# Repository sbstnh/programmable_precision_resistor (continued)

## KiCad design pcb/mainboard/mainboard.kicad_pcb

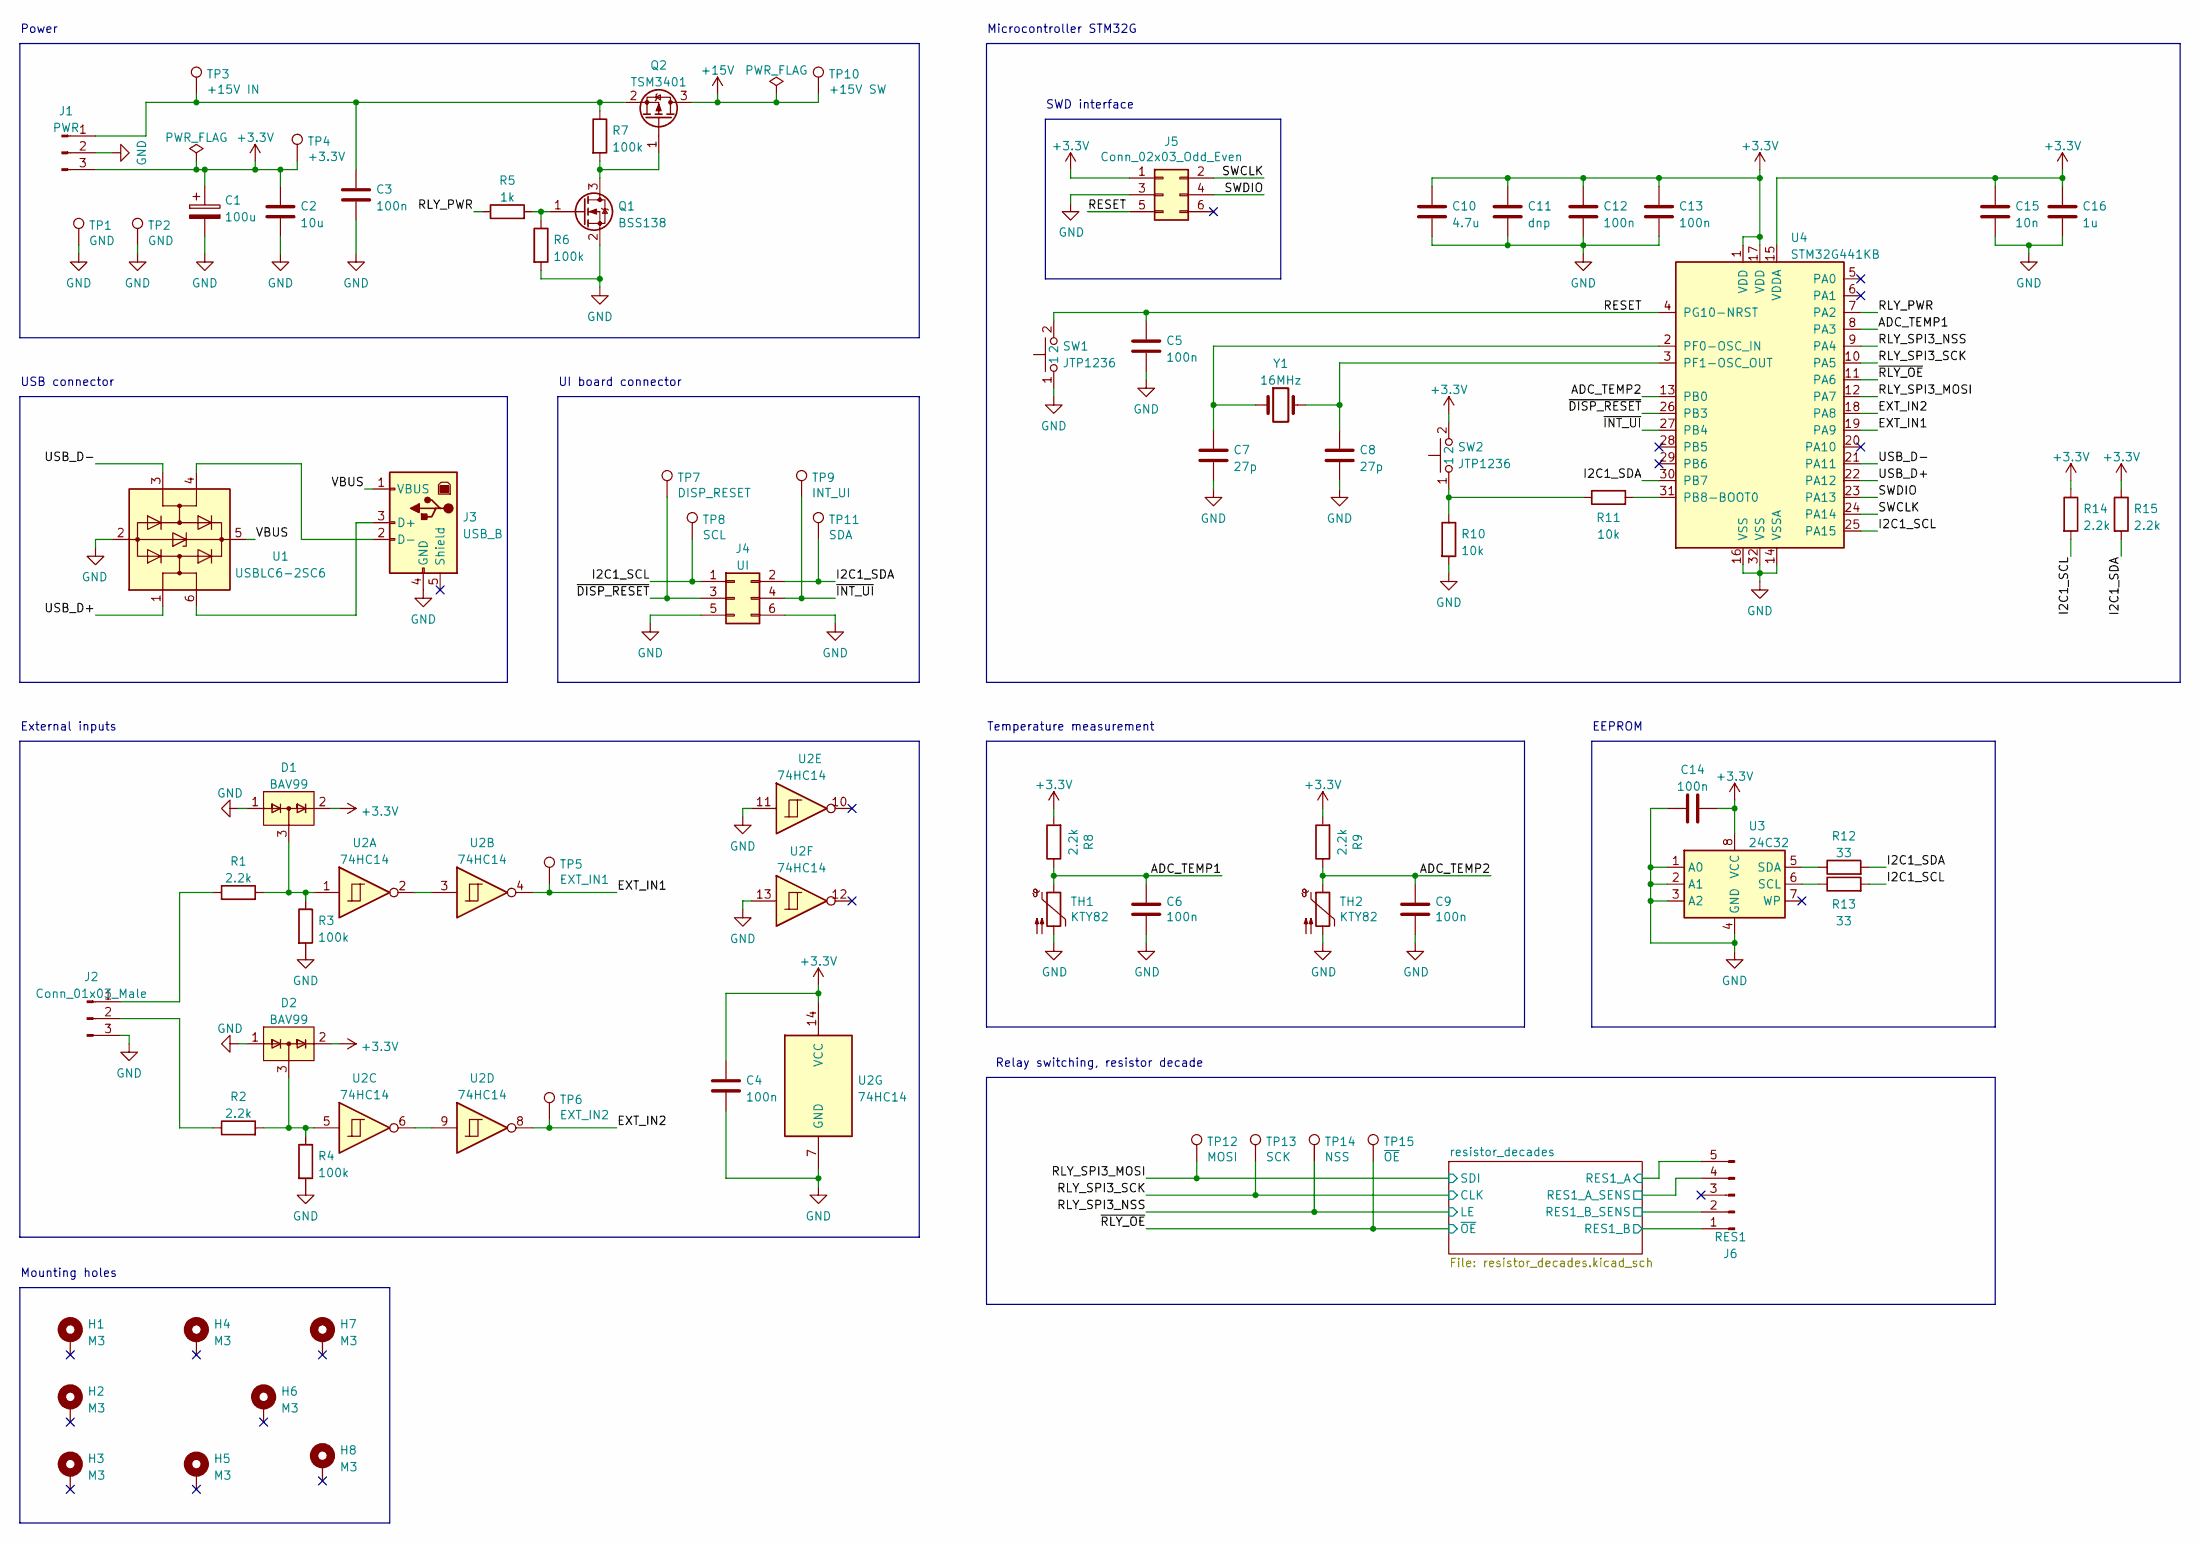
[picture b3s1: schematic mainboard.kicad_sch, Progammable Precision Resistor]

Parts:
C1: 100u; CP_EIA-7343-31_Kemet-D_Pad2.25x2.55mm_HandSolder
C2: 10u; C_0805_2012Metric_Box
C3, C4, C5, C6, C9, C12, C13, C14: 100n; C_0805_2012Metric_Box
C7, C8: 27p; C_0805_2012Metric_Box
C10: 4.7u; C_0805_2012Metric_Box
C11: dnp; C_0805_2012Metric_Box
C15: 10n; C_0805_2012Metric_Box
C16: 1u; C_0805_2012Metric_Box
D1, D2: BAV99; SOT-23
H1, H2, H3, H4, H5, H6, H7, H8: M3; MountingHole_3.2mm_M3_DIN965_Pad
J1: PWR; Molex_KK-254_AE-6410-03A_1x03_P2.54mm_Vertical
J2: Conn_01x03_Male; PhoenixContact_MSTBA_2,5_3-G_1x03_P5.00mm_Horizontal
J3: USB_B; USB_B_Lumberg_2411_02_Horizontal
J4: UI; IDC-Header_2x03_P2.54mm_Vertical
J5: Conn_02x03_Odd_Even; IDC-Header_2x03_P2.54mm_Vertical
J6: RES1; Molex_KK-396_A-41791-0005_1x05_P3.96mm_Vertical
Q1: BSS138; SOT-23
Q2: TSM3401; SOT-23
R1, R2, R8, R9, R14, R15: 2.2k; R_0805_2012Metric_Box
R3, R4, R6, R7: 100k; R_0805_2012Metric_Box
R5: 1k; R_0805_2012Metric_Box
R10, R11: 10k; R_0805_2012Metric_Box
R12, R13: 33; R_0805_2012Metric_Box
SW1, SW2: JTP1236
TH1, TH2: KTY82; SOT-23
TP1, TP2: GND; TestPoint_Loop_D1.80mm_Drill1.0mm_Beaded
TP3: +15V IN; TestPoint_Loop_D1.80mm_Drill1.0mm_Beaded
TP4: +3.3V; TestPoint_Loop_D1.80mm_Drill1.0mm_Beaded
TP5: EXT_IN1; TestPoint_Loop_D1.80mm_Drill1.0mm_Beaded
TP6: EXT_IN2; TestPoint_Loop_D1.80mm_Drill1.0mm_Beaded
TP7: DISP_RESET; TestPoint_Loop_D1.80mm_Drill1.0mm_Beaded
TP8: SCL; TestPoint_Loop_D1.80mm_Drill1.0mm_Beaded
TP9: INT_UI; TestPoint_Loop_D1.80mm_Drill1.0mm_Beaded
TP10: +15V SW; TestPoint_Loop_D1.80mm_Drill1.0mm_Beaded
TP11: SDA; TestPoint_Loop_D1.80mm_Drill1.0mm_Beaded
TP12: MOSI; TestPoint_Loop_D1.80mm_Drill1.0mm_Beaded
TP13: SCK; TestPoint_Loop_D1.80mm_Drill1.0mm_Beaded
TP14: NSS; TestPoint_Loop_D1.80mm_Drill1.0mm_Beaded
TP15: ~{OE}; TestPoint_Loop_D1.80mm_Drill1.0mm_Beaded
U1: USBLC6-2SC6; SOT-23-6
U2: 74HC14; SOIC-14_3.9x8.7mm_P1.27mm
U3: 24C32; SO-8_3.9x4.9mm_P1.27mm
U4: STM32G441KB; LQFP-32_7x7mm_P0.8mm
Y1: 16MHz; Crystal_HC49-4H_Vertical

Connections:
+3.3V: C1.1, C2.1, C4.1, C10.1, C11.1, C12.1, C13.1, C14.2, C15.1, C16.1, D1.2 (A), D2.2 (A), J1.3, J5.1, R8.2, R9.2, R14.1, R15.1, SW2.2, TP4.1, U2.14 (VCC), U3.8 (VCC), U4.1 (VDD), U4.15 (VDDA), U4.17 (VDD); also elsewhere on the board
+15V: Q2.3 (D), TP10.1; also elsewhere on the board
/ADC_TEMP1: C6.1, R8.1, TH1.1, U4.8 (PA3)
/ADC_TEMP2: C9.1, R9.1, TH2.1, U4.13 (PB0)
/EXT_IN1: TP5.1, U2.4, U4.19 (PA9)
/EXT_IN2: TP6.1, U2.8, U4.18 (PA8)
/I2C1_SCL: J4.1, R13.2, R14.2, TP8.1, U4.25 (PA15)
/I2C1_SDA: J4.2, R12.2, R15.2, TP11.1, U4.30 (PB7)
/RESET: C5.1, J5.5, SW1.2, U4.4 (PG10-NRST)
/RLY_PWR: R5.1, U4.7 (PA2)
/RLY_SPI3_MOSI: TP12.1, U4.12 (PA7); also elsewhere on the board
/RLY_SPI3_NSS: TP14.1, U4.9 (PA4); also elsewhere on the board
/RLY_SPI3_SCK: TP13.1, U4.10 (PA5); also elsewhere on the board
/SWCLK: J5.2, U4.24 (PA14)
/SWDIO: J5.4, U4.23 (PA13)
/USB_D+: U1.1 (I/O1), U4.22 (PA12)
/USB_D-: U1.3 (I/O2), U4.21 (PA11)
/VBUS: J3.1 (VBUS), U1.5 (VBUS)
/resistor_decades/RES1_A: J6.4, J6.5; also elsewhere on the board
/resistor_decades/RES1_B: J6.1, J6.2; also elsewhere on the board
/~DISP_RESET: J4.3, TP7.1, U4.26 (PB3)
/~INT_UI: J4.4, TP9.1, U4.27 (PB4)
/~RLY_OE: TP15.1, U4.11 (PA6); also elsewhere on the board
GND: C1.2, C2.2, C3.2, C4.2, C5.2, C6.2, C7.2, C8.2, C9.2, C10.2, C11.2, C12.2, C13.2, C14.1, C15.2, C16.2, D1.1 (K), D2.1 (K), J1.2, J2.3, J3.4 (GND), J4.5, J4.6, J5.3, Q1.2 (S), R3.2, R4.2, R6.2, R10.2, SW1.1, TH1.2, TH2.2, TP1.1, TP2.1, U1.2 (GND), U2.7 (GND), U2.11, U2.13, U3.1 (A0), U3.2 (A1), U3.3 (A2), U3.4 (GND), U4.14 (VSSA), U4.16 (VSS), U4.32 (VSS); also elsewhere on the board
unnamed: D1.3 (K), R1.2, R3.1, U2.1
unnamed: D2.3 (K), R2.2, R4.1, U2.5
unnamed: C3.1, J1.1, Q2.2 (S), R7.1, TP3.1
unnamed: J2.1, R1.1
unnamed: J2.2, R2.1
unnamed: J3.3 (D+), U1.6 (I/O1)
unnamed: J3.2 (D-), U1.4 (I/O2)
unnamed: Q1.3 (D), Q2.1 (G), R7.2
unnamed: Q1.1 (G), R5.2, R6.1
unnamed: R10.1, R11.1, SW2.1
unnamed: U2.2, U2.3
unnamed: U2.6, U2.9
unnamed: R13.1, U3.6 (SCL)
unnamed: R12.1, U3.5 (SDA)
unnamed: R11.2, U4.31 (PB8-BOOT0)
unnamed: C7.1, U4.2 (PF0-OSC_IN), Y1.1
unnamed: C8.1, U4.3 (PF1-OSC_OUT), Y1.2

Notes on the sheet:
EEPROM
Power
Microcontroller STM32G
Mounting holes
USB connector
External inputs
Temperature measurement
Relay switching, resistor decade
SWD interface
UI board connector

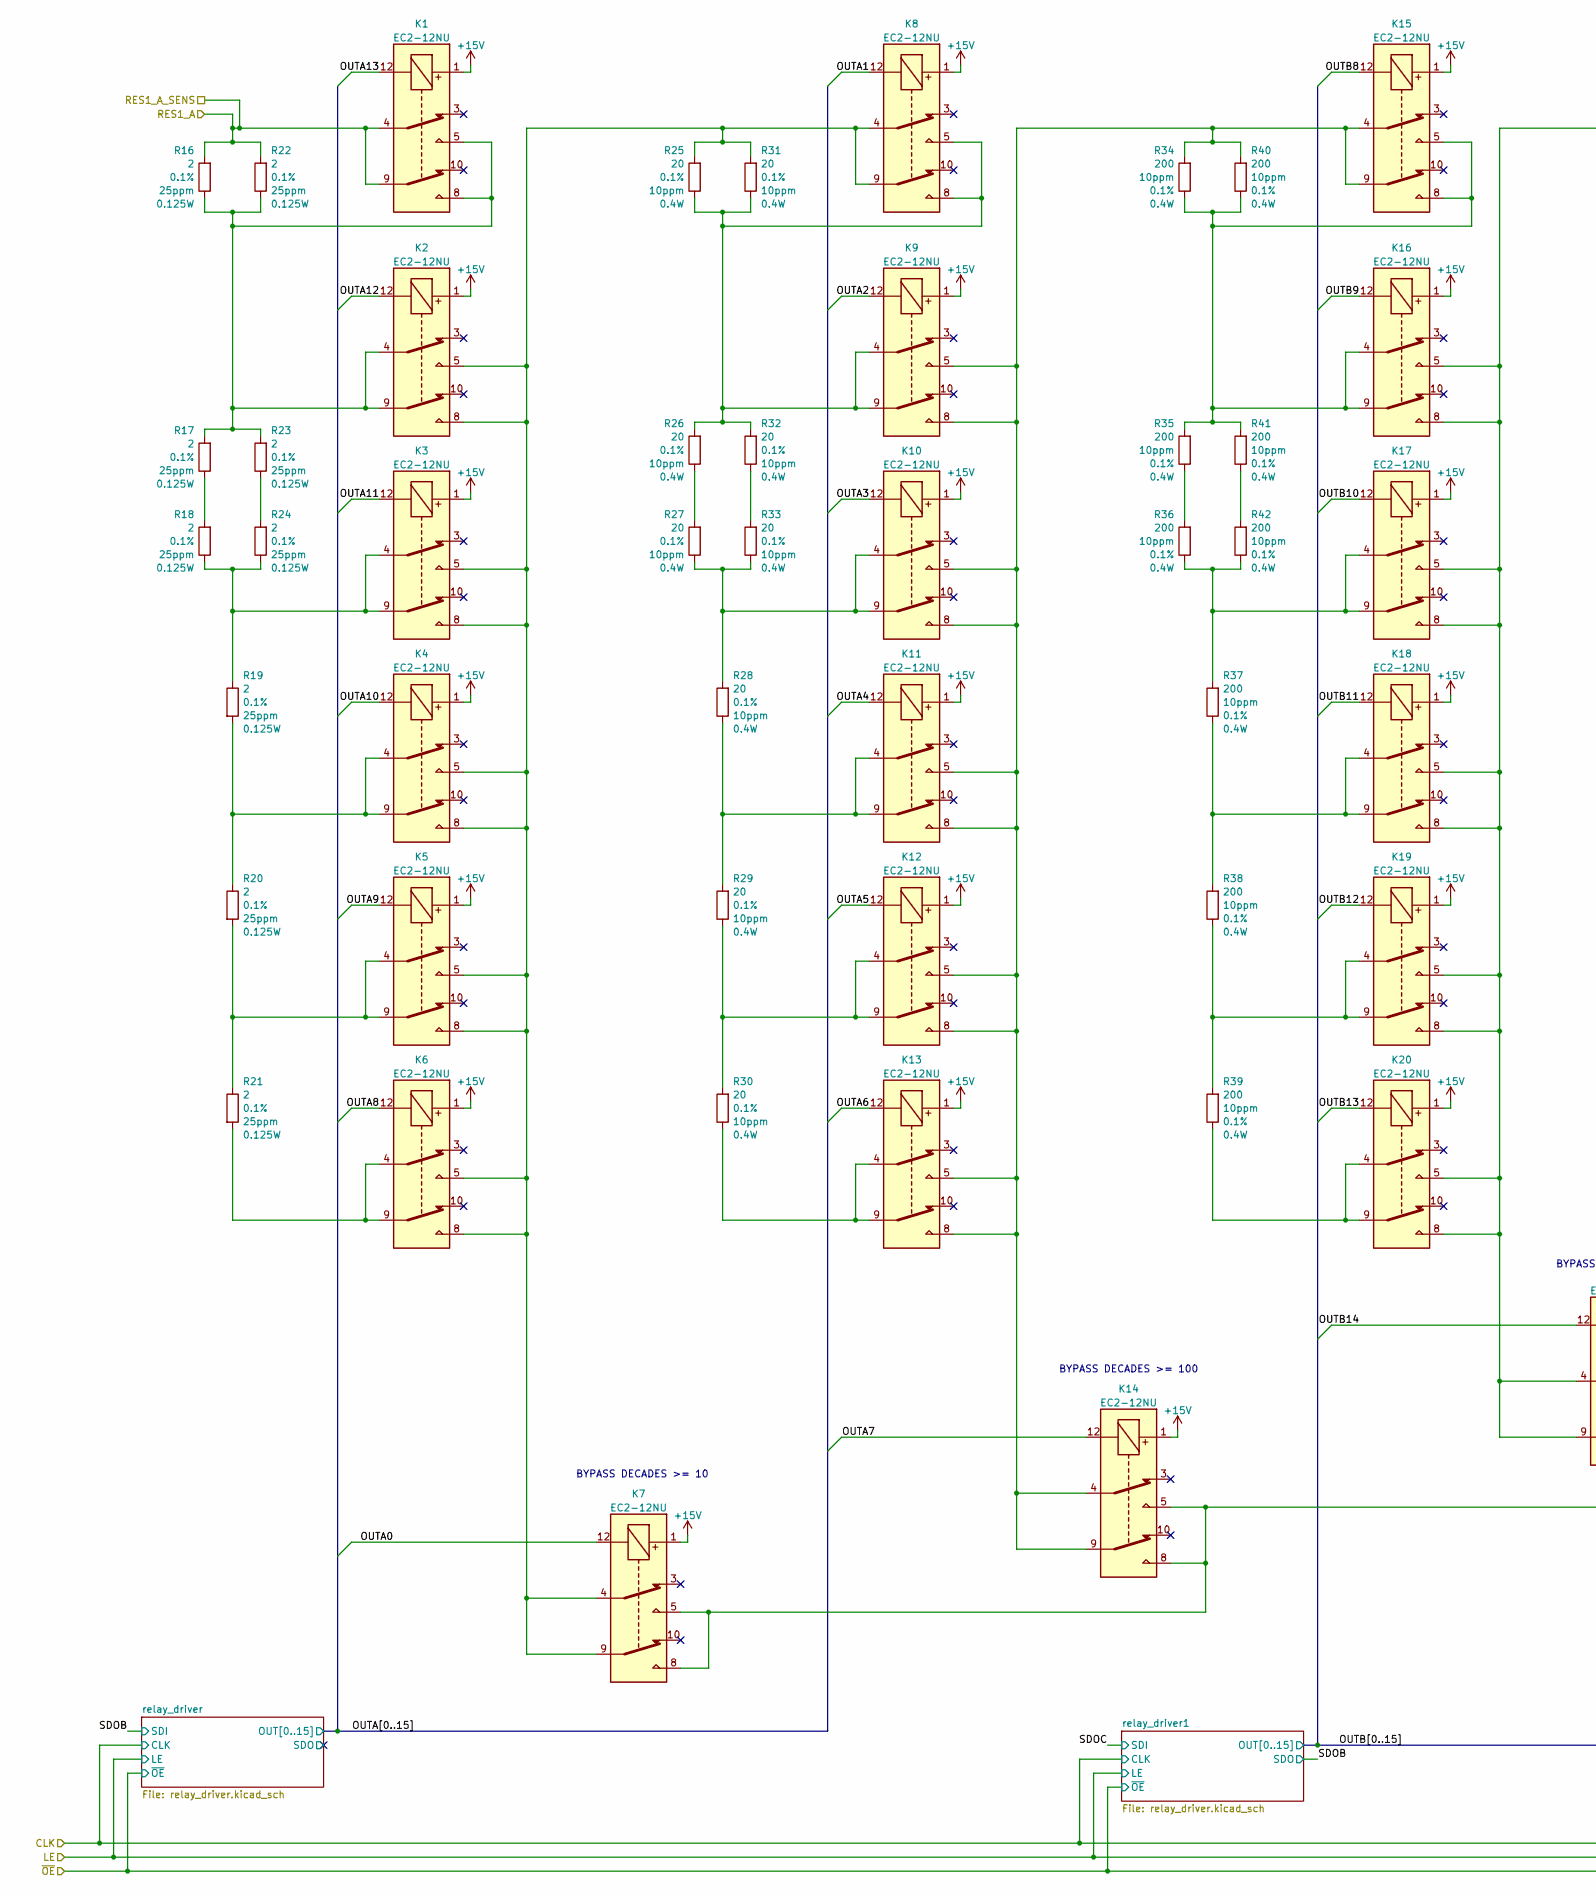
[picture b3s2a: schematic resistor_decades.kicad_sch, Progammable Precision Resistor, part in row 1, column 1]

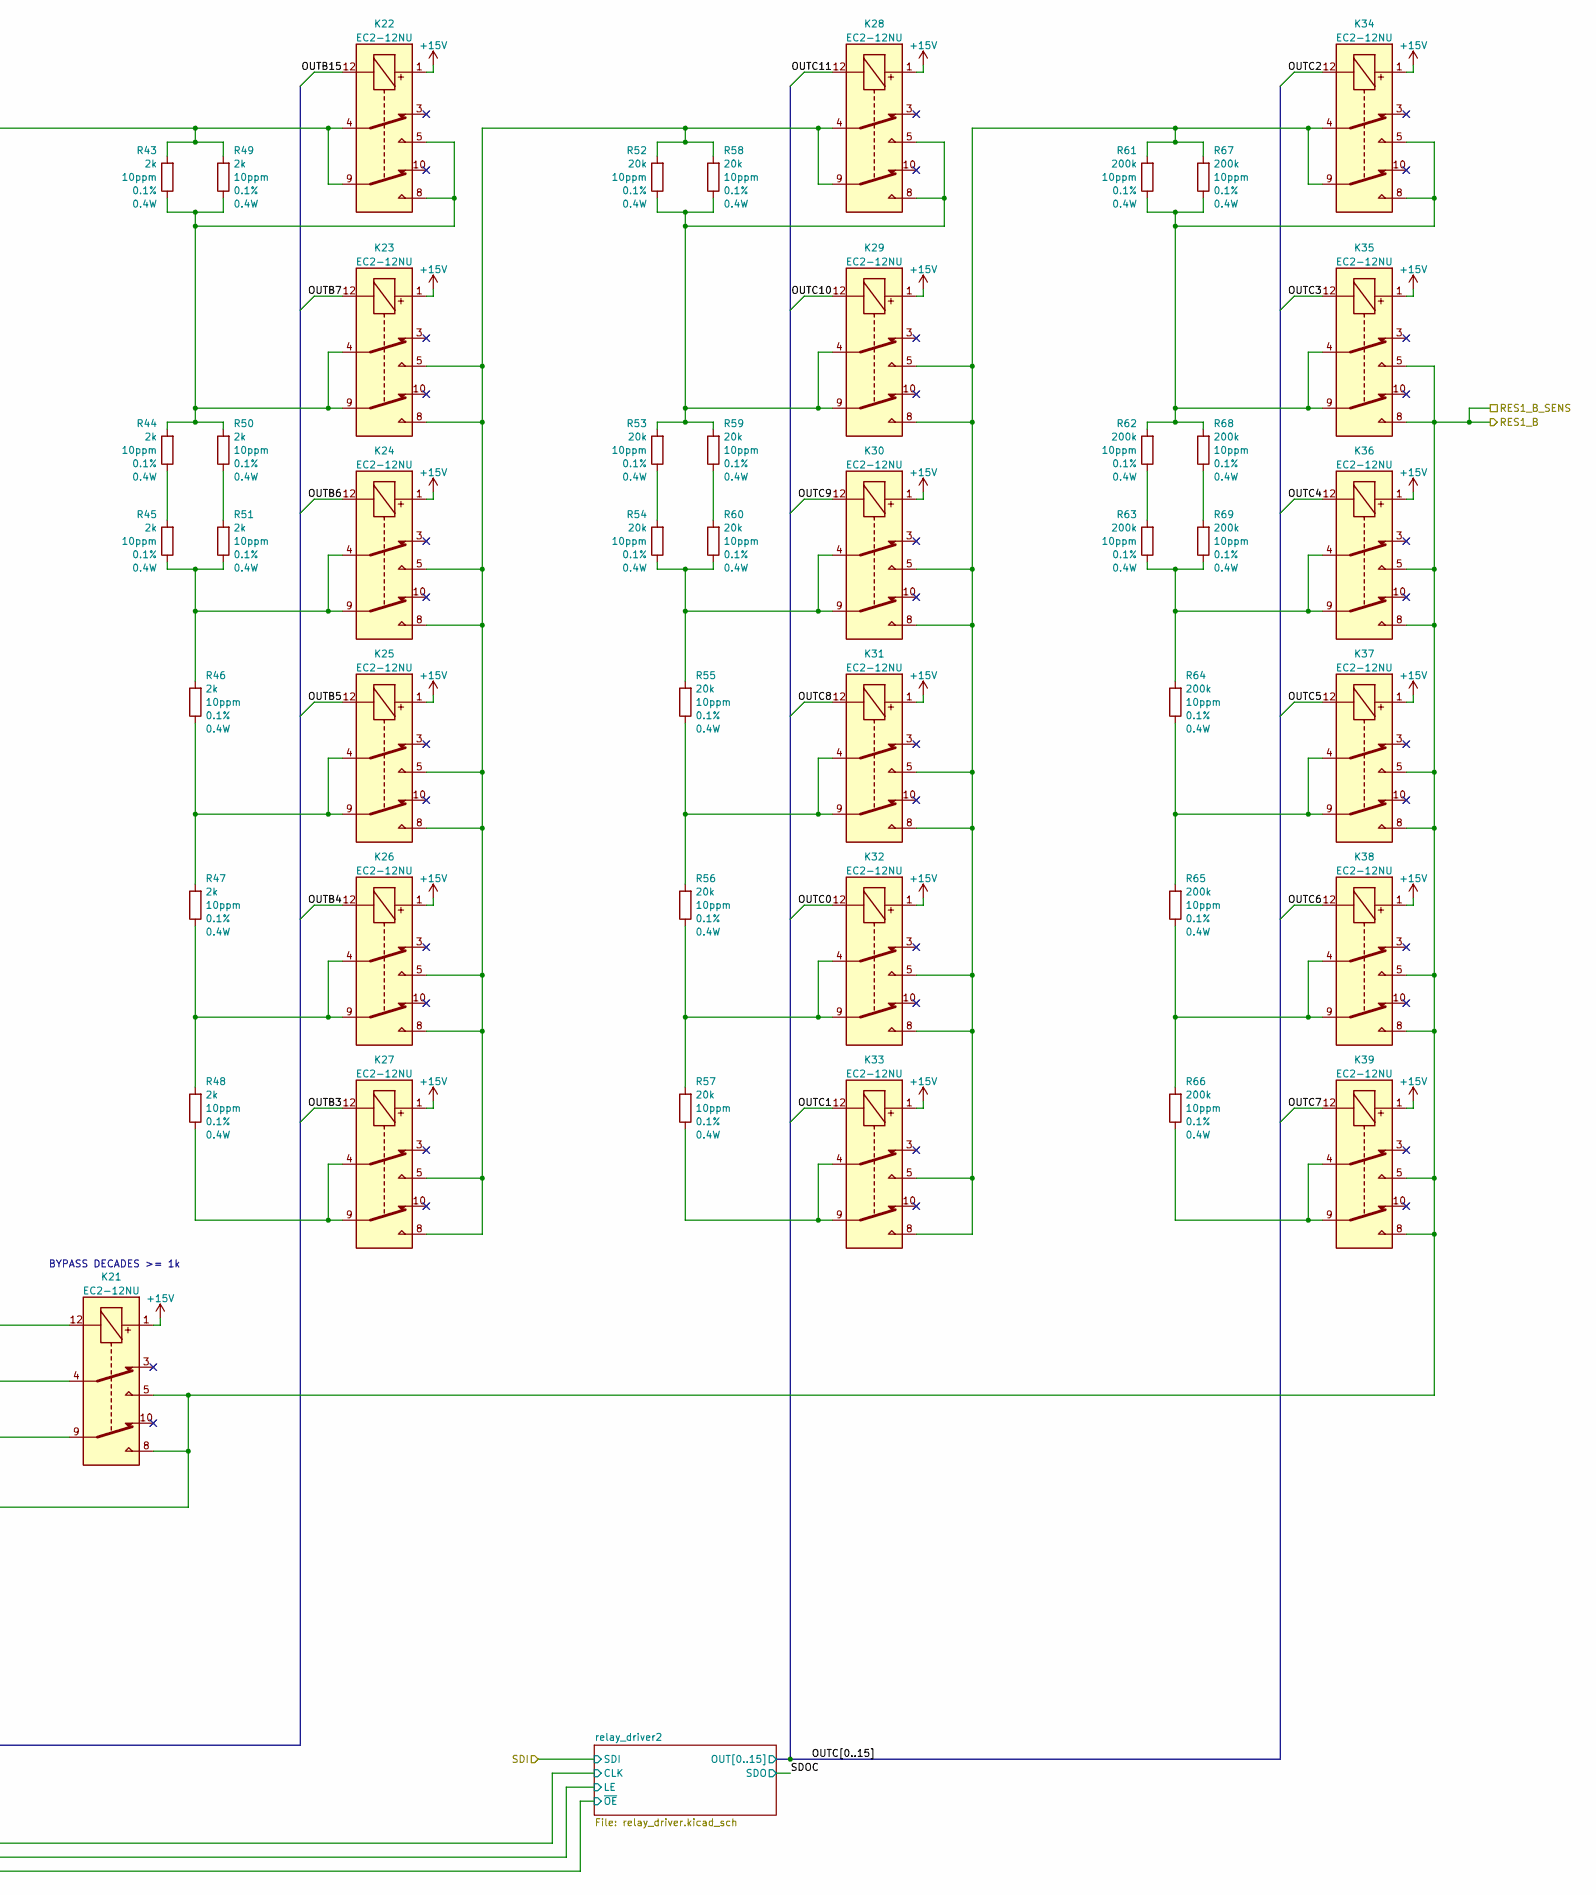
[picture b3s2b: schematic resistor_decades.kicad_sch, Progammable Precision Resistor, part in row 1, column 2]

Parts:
K1, K2, K3, K4, K5, K6, K7, K8, K9, K10, K11, K12, K13, K14, K15, K16, K17, K18, K19, K20, K21, K22, K23, K24, K25, K26, K27, K28, K29, K30, K31, K32, K33, K34, K35, K36, K37, K38, K39: EC2-12NU; Relay_DPDT_Kemet_EC2
R16, R17, R18, R19, R20, R21, R22, R23, R24: 2; R_1206_3216Metric_Box; Tolerance 0.1%
R25, R26, R27, R28, R29, R30, R31, R32, R33: 20; R_1206_3216Metric_Box; Tolerance 0.1%
R34, R35, R36, R37, R38, R39, R40, R41, R42: 200; R_1206_3216Metric_Box; Tolerance 0.1%
R43, R44, R45, R46, R47, R48, R49, R50, R51: 2k; R_1206_3216Metric_Box; Tolerance 0.1%
R52, R53, R54, R55, R56, R57, R58, R59, R60: 20k; R_1206_3216Metric_Box; Tolerance 0.1%
R61, R62, R63, R64, R65, R66, R67, R68, R69: 200k; R_1206_3216Metric_Box; Tolerance 0.1%

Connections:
+15V: K1.1, K2.1, K3.1, K4.1, K5.1, K6.1, K7.1, K8.1, K9.1, K10.1, K11.1, K12.1, K13.1, K14.1, K15.1, K16.1, K17.1, K18.1, K19.1, K20.1, K21.1, K22.1, K23.1, K24.1, K25.1, K26.1, K27.1, K28.1, K29.1, K30.1, K31.1, K32.1, K33.1, K34.1, K35.1, K36.1, K37.1, K38.1, K39.1; also elsewhere on the board
/resistor_decades/OUTA0: K7.12; also elsewhere on the board
/resistor_decades/OUTA1: K8.12; also elsewhere on the board
/resistor_decades/OUTA2: K9.12; also elsewhere on the board
/resistor_decades/OUTA3: K10.12; also elsewhere on the board
/resistor_decades/OUTA4: K11.12; also elsewhere on the board
/resistor_decades/OUTA5: K12.12; also elsewhere on the board
/resistor_decades/OUTA6: K13.12; also elsewhere on the board
/resistor_decades/OUTA7: K14.12; also elsewhere on the board
/resistor_decades/OUTA8: K6.12; also elsewhere on the board
/resistor_decades/OUTA9: K5.12; also elsewhere on the board
/resistor_decades/OUTA10: K4.12; also elsewhere on the board
/resistor_decades/OUTA11: K3.12; also elsewhere on the board
/resistor_decades/OUTA12: K2.12; also elsewhere on the board
/resistor_decades/OUTA13: K1.12; also elsewhere on the board
/resistor_decades/OUTB3: K27.12; also elsewhere on the board
/resistor_decades/OUTB4: K26.12; also elsewhere on the board
/resistor_decades/OUTB5: K25.12; also elsewhere on the board
/resistor_decades/OUTB6: K24.12; also elsewhere on the board
/resistor_decades/OUTB7: K23.12; also elsewhere on the board
/resistor_decades/OUTB8: K15.12; also elsewhere on the board
/resistor_decades/OUTB9: K16.12; also elsewhere on the board
/resistor_decades/OUTB10: K17.12; also elsewhere on the board
/resistor_decades/OUTB11: K18.12; also elsewhere on the board
/resistor_decades/OUTB12: K19.12; also elsewhere on the board
/resistor_decades/OUTB13: K20.12; also elsewhere on the board
/resistor_decades/OUTB14: K21.12; also elsewhere on the board
/resistor_decades/OUTB15: K22.12; also elsewhere on the board
/resistor_decades/OUTC0: K32.12; also elsewhere on the board
/resistor_decades/OUTC1: K33.12; also elsewhere on the board
/resistor_decades/OUTC2: K34.12; also elsewhere on the board
/resistor_decades/OUTC3: K35.12; also elsewhere on the board
/resistor_decades/OUTC4: K36.12; also elsewhere on the board
/resistor_decades/OUTC5: K37.12; also elsewhere on the board
/resistor_decades/OUTC6: K38.12; also elsewhere on the board
/resistor_decades/OUTC7: K39.12; also elsewhere on the board
/resistor_decades/OUTC8: K31.12; also elsewhere on the board
/resistor_decades/OUTC9: K30.12; also elsewhere on the board
/resistor_decades/OUTC10: K29.12; also elsewhere on the board
/resistor_decades/OUTC11: K28.12; also elsewhere on the board
/resistor_decades/RES1_A: K1.4, K1.9, R16.2, R22.2; also elsewhere on the board
/resistor_decades/RES1_B: K7.5, K7.8, K14.5, K14.8, K21.5, K21.8, K35.5, K35.8, K36.5, K36.8, K37.5, K37.8, K38.5, K38.8, K39.5, K39.8; also elsewhere on the board
unnamed: K1.5, K1.8, K2.4, K2.9, R16.1, R17.2, R22.1, R23.2
unnamed: K2.5, K2.8, K3.5, K3.8, K4.5, K4.8, K5.5, K5.8, K6.5, K6.8, K7.4, K7.9, K8.4, K8.9, R25.2, R31.2
unnamed: K3.4, K3.9, R18.1, R19.1, R24.1
unnamed: K4.4, K4.9, R19.2, R20.1
unnamed: K5.4, K5.9, R20.2, R21.1
unnamed: K6.4, K6.9, R21.2
unnamed: K8.5, K8.8, K9.4, K9.9, R25.1, R26.2, R31.1, R32.2
unnamed: K10.4, K10.9, R27.1, R28.2, R33.1
unnamed: K9.5, K9.8, K10.5, K10.8, K11.5, K11.8, K12.5, K12.8, K13.5, K13.8, K14.4, K14.9, K15.4, K15.9, R34.2, R40.2
unnamed: K11.4, K11.9, R28.1, R29.2
unnamed: K12.4, K12.9, R29.1, R30.2
unnamed: K13.4, K13.9, R30.1
unnamed: K15.5, K15.8, K16.4, K16.9, R34.1, R35.2, R40.1, R41.2
unnamed: K16.5, K16.8, K17.5, K17.8, K18.5, K18.8, K19.5, K19.8, K20.5, K20.8, K21.4, K21.9, K22.4, K22.9, R43.2, R49.2
unnamed: K17.4, K17.9, R36.1, R37.2, R42.1
unnamed: K18.4, K18.9, R37.1, R38.2
unnamed: K19.4, K19.9, R38.1, R39.2
unnamed: K20.4, K20.9, R39.1
unnamed: K22.5, K22.8, K23.4, K23.9, R43.1, R44.2, R49.1, R50.2
unnamed: K23.5, K23.8, K24.5, K24.8, K25.5, K25.8, K26.5, K26.8, K27.5, K27.8, K28.4, K28.9, R52.2, R58.2
unnamed: K24.4, K24.9, R45.1, R46.2, R51.1
unnamed: K25.4, K25.9, R46.1, R47.2
unnamed: K26.4, K26.9, R47.1, R48.2
unnamed: K27.4, K27.9, R48.1
unnamed: K28.5, K28.8, K29.4, K29.9, R52.1, R53.2, R58.1, R59.2
unnamed: K29.5, K29.8, K30.5, K30.8, K31.5, K31.8, K32.5, K32.8, K33.5, K33.8, K34.4, K34.9, R61.2, R67.2
unnamed: K30.4, K30.9, R54.1, R55.2, R60.1
unnamed: K31.4, K31.9, R55.1, R56.2
unnamed: K32.4, K32.9, R56.1, R57.2
unnamed: K33.4, K33.9, R57.1
unnamed: K34.5, K34.8, K35.4, K35.9, R61.1, R62.2, R67.1, R68.2
unnamed: K36.4, K36.9, R63.1, R64.2, R69.1
unnamed: K37.4, K37.9, R64.1, R65.2
unnamed: K38.4, K38.9, R65.1, R66.2
unnamed: K39.4, K39.9, R66.1
unnamed: R17.1, R18.2
unnamed: R23.1, R24.2
unnamed: R26.1, R27.2
unnamed: R32.1, R33.2
unnamed: R35.1, R36.2
unnamed: R41.1, R42.2
unnamed: R44.1, R45.2
unnamed: R50.1, R51.2
unnamed: R53.1, R54.2
unnamed: R59.1, R60.2
unnamed: R62.1, R63.2
unnamed: R68.1, R69.2

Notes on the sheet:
BYPASS DECADES >= 1k
BYPASS DECADES >= 100
BYPASS DECADES >= 10

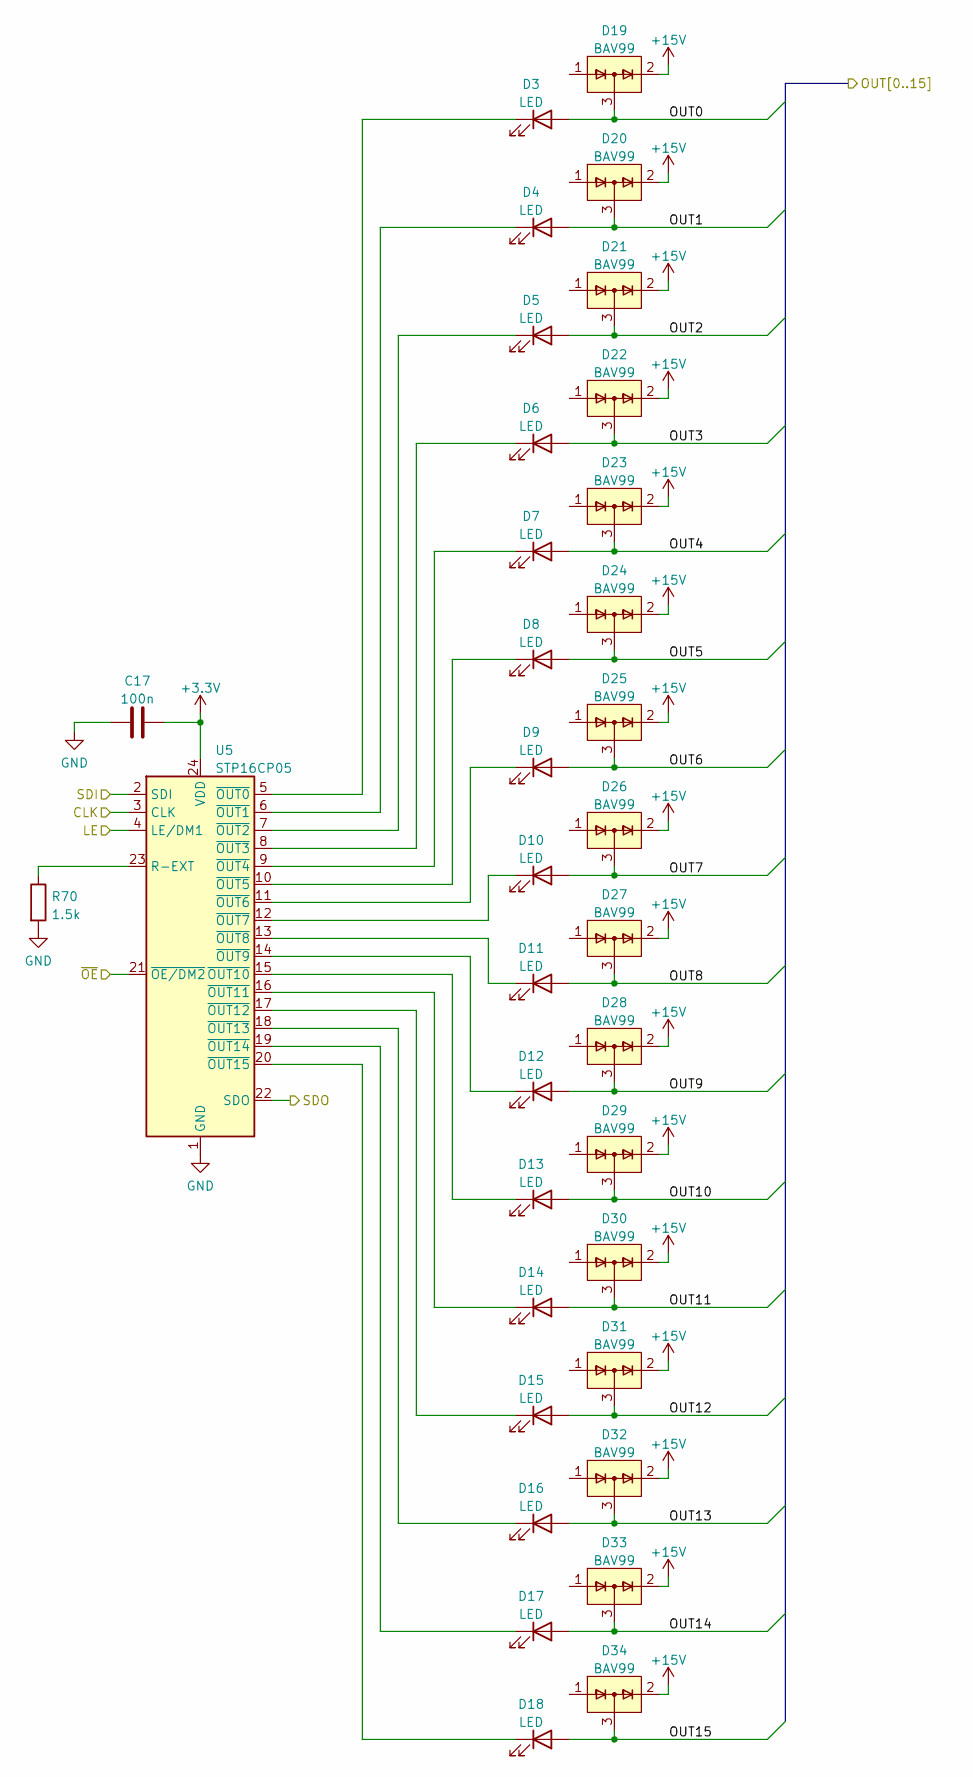
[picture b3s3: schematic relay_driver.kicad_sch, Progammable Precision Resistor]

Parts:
C17: 100n; C_0805_2012Metric_Box
D3, D4, D5, D6, D7, D8, D9, D10, D11, D12, D13, D14, D15, D16, D17, D18: LED; LED_0805_2012Metric
D19, D20, D21, D22, D23, D24, D25, D26, D27, D28, D29, D30, D31, D32, D33, D34: BAV99; SOT-23
R70: 1.5k; R_0805_2012Metric_Box
U5: STP16CP05; TSSOP-24_4.4x7.8mm_P0.65mm

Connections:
+3.3V: C17.2, U5.24 (VDD); also elsewhere on the board
+15V: D19.2 (A), D20.2 (A), D21.2 (A), D22.2 (A), D23.2 (A), D24.2 (A), D25.2 (A), D26.2 (A), D27.2 (A), D28.2 (A), D29.2 (A), D30.2 (A), D31.2 (A), D32.2 (A); also elsewhere on the board
/RLY_SPI3_NSS: U5.4 (LE/DM1); also elsewhere on the board
/RLY_SPI3_SCK: U5.3 (CLK); also elsewhere on the board
/resistor_decades/OUTA0: D3.2 (A), D19.3 (K); also elsewhere on the board
/resistor_decades/OUTA1: D4.2 (A), D20.3 (K); also elsewhere on the board
/resistor_decades/OUTA2: D5.2 (A), D21.3 (K); also elsewhere on the board
/resistor_decades/OUTA3: D6.2 (A), D22.3 (K); also elsewhere on the board
/resistor_decades/OUTA4: D7.2 (A), D23.3 (K); also elsewhere on the board
/resistor_decades/OUTA5: D8.2 (A), D24.3 (K); also elsewhere on the board
/resistor_decades/OUTA6: D9.2 (A), D25.3 (K); also elsewhere on the board
/resistor_decades/OUTA7: D10.2 (A), D26.3 (K); also elsewhere on the board
/resistor_decades/OUTA8: D11.2 (A), D27.3 (K); also elsewhere on the board
/resistor_decades/OUTA9: D12.2 (A), D28.3 (K); also elsewhere on the board
/resistor_decades/OUTA10: D13.2 (A), D29.3 (K); also elsewhere on the board
/resistor_decades/OUTA11: D14.2 (A), D30.3 (K); also elsewhere on the board
/resistor_decades/OUTA12: D15.2 (A), D31.3 (K); also elsewhere on the board
/resistor_decades/OUTA13: D16.2 (A), D32.3 (K); also elsewhere on the board
/resistor_decades/SDOB: U5.2 (SDI); also elsewhere on the board
/resistor_decades/relay_driver/SDO: U5.22 (SDO)
/~RLY_OE: U5.21 (~OE/DM2); also elsewhere on the board
GND: C17.1, R70.2, U5.1 (GND); also elsewhere on the board
unnamed: D3.1 (K), U5.5 (~OUT0)
unnamed: D4.1 (K), U5.6 (~OUT1)
unnamed: D5.1 (K), U5.7 (~OUT2)
unnamed: D6.1 (K), U5.8 (~OUT3)
unnamed: D7.1 (K), U5.9 (~OUT4)
unnamed: D8.1 (K), U5.10 (~OUT5)
unnamed: D9.1 (K), U5.11 (~OUT6)
unnamed: D10.1 (K), U5.12 (~OUT7)
unnamed: D11.1 (K), U5.13 (~OUT8)
unnamed: D12.1 (K), U5.14 (~OUT9)
unnamed: D13.1 (K), U5.15 (~OUT10)
unnamed: D14.1 (K), U5.16 (~OUT11)
unnamed: D15.1 (K), U5.17 (~OUT12)
unnamed: D16.1 (K), U5.18 (~OUT13)
unnamed: R70.1, U5.23 (R-EXT)

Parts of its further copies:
C18, C19: 100n; C_0805_2012Metric_Box
D38, D39, D40, D41, D42, D43, D44, D45, D46, D47, D48, D49, D50, D67, D68, D69, D70, D71, D72, D73, D74, D75, D76, D77, D78: LED; LED_0805_2012Metric
D54, D55, D56, D57, D58, D59, D60, D61, D62, D63, D64, D65, D66, D83, D84, D85, D86, D87, D88, D89, D90, D91, D92, D93, D94: BAV99; SOT-23
R71, R72: 1.5k; R_0805_2012Metric_Box
U6, U7: STP16CP05; TSSOP-24_4.4x7.8mm_P0.65mm

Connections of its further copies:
+3.3V: C18.2, C19.2, U6.24 (VDD), U7.24 (VDD); also elsewhere on the board
+15V: D54.2 (A), D55.2 (A), D56.2 (A), D57.2 (A), D58.2 (A), D59.2 (A), D60.2 (A), D61.2 (A), D62.2 (A), D63.2 (A), D64.2 (A), D65.2 (A), D66.2 (A), D83.2 (A), D84.2 (A), D85.2 (A), D86.2 (A), D87.2 (A), D88.2 (A), D89.2 (A), D90.2 (A), D91.2 (A), D92.2 (A), D93.2 (A), D94.2 (A); also elsewhere on the board
/RLY_SPI3_MOSI: U7.2 (SDI); also elsewhere on the board
/RLY_SPI3_NSS: U6.4 (LE/DM1), U7.4 (LE/DM1); also elsewhere on the board
/RLY_SPI3_SCK: U6.3 (CLK), U7.3 (CLK); also elsewhere on the board
/resistor_decades/OUTB3: D38.2 (A), D54.3 (K); also elsewhere on the board
/resistor_decades/OUTB4: D39.2 (A), D55.3 (K); also elsewhere on the board
/resistor_decades/OUTB5: D40.2 (A), D56.3 (K); also elsewhere on the board
/resistor_decades/OUTB6: D41.2 (A), D57.3 (K); also elsewhere on the board
/resistor_decades/OUTB7: D42.2 (A), D58.3 (K); also elsewhere on the board
/resistor_decades/OUTB8: D43.2 (A), D59.3 (K); also elsewhere on the board
/resistor_decades/OUTB9: D44.2 (A), D60.3 (K); also elsewhere on the board
/resistor_decades/OUTB10: D45.2 (A), D61.3 (K); also elsewhere on the board
/resistor_decades/OUTB11: D46.2 (A), D62.3 (K); also elsewhere on the board
/resistor_decades/OUTB12: D47.2 (A), D63.3 (K); also elsewhere on the board
/resistor_decades/OUTB13: D48.2 (A), D64.3 (K); also elsewhere on the board
/resistor_decades/OUTB14: D49.2 (A), D65.3 (K); also elsewhere on the board
/resistor_decades/OUTB15: D50.2 (A), D66.3 (K); also elsewhere on the board
/resistor_decades/OUTC0: D67.2 (A), D83.3 (K); also elsewhere on the board
/resistor_decades/OUTC1: D68.2 (A), D84.3 (K); also elsewhere on the board
/resistor_decades/OUTC2: D69.2 (A), D85.3 (K); also elsewhere on the board
/resistor_decades/OUTC3: D70.2 (A), D86.3 (K); also elsewhere on the board
/resistor_decades/OUTC4: D71.2 (A), D87.3 (K); also elsewhere on the board
/resistor_decades/OUTC5: D72.2 (A), D88.3 (K); also elsewhere on the board
/resistor_decades/OUTC6: D73.2 (A), D89.3 (K); also elsewhere on the board
/resistor_decades/OUTC7: D74.2 (A), D90.3 (K); also elsewhere on the board
/resistor_decades/OUTC8: D75.2 (A), D91.3 (K); also elsewhere on the board
/resistor_decades/OUTC9: D76.2 (A), D92.3 (K); also elsewhere on the board
/resistor_decades/OUTC10: D77.2 (A), D93.3 (K); also elsewhere on the board
/resistor_decades/OUTC11: D78.2 (A), D94.3 (K); also elsewhere on the board
/resistor_decades/SDOB: U6.22 (SDO); also elsewhere on the board
/resistor_decades/SDOC: U6.2 (SDI), U7.22 (SDO)
/~RLY_OE: U6.21 (~OE/DM2), U7.21 (~OE/DM2); also elsewhere on the board
GND: C18.1, C19.1, R71.2, R72.2, U6.1 (GND), U7.1 (GND); also elsewhere on the board
unnamed: D38.1 (K), U6.8 (~OUT3)
unnamed: D39.1 (K), U6.9 (~OUT4)
unnamed: D40.1 (K), U6.10 (~OUT5)
unnamed: D41.1 (K), U6.11 (~OUT6)
unnamed: D42.1 (K), U6.12 (~OUT7)
unnamed: D43.1 (K), U6.13 (~OUT8)
unnamed: D44.1 (K), U6.14 (~OUT9)
unnamed: D45.1 (K), U6.15 (~OUT10)
unnamed: D46.1 (K), U6.16 (~OUT11)
unnamed: D47.1 (K), U6.17 (~OUT12)
unnamed: D48.1 (K), U6.18 (~OUT13)
unnamed: D67.1 (K), U7.5 (~OUT0)
unnamed: D68.1 (K), U7.6 (~OUT1)
unnamed: D69.1 (K), U7.7 (~OUT2)
unnamed: D70.1 (K), U7.8 (~OUT3)
unnamed: D71.1 (K), U7.9 (~OUT4)
unnamed: D72.1 (K), U7.10 (~OUT5)
unnamed: D73.1 (K), U7.11 (~OUT6)
unnamed: D74.1 (K), U7.12 (~OUT7)
unnamed: D75.1 (K), U7.13 (~OUT8)
unnamed: D76.1 (K), U7.14 (~OUT9)
unnamed: D77.1 (K), U7.15 (~OUT10)
unnamed: D78.1 (K), U7.16 (~OUT11)
unnamed: R71.1, U6.23 (R-EXT)
unnamed: R72.1, U7.23 (R-EXT)

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
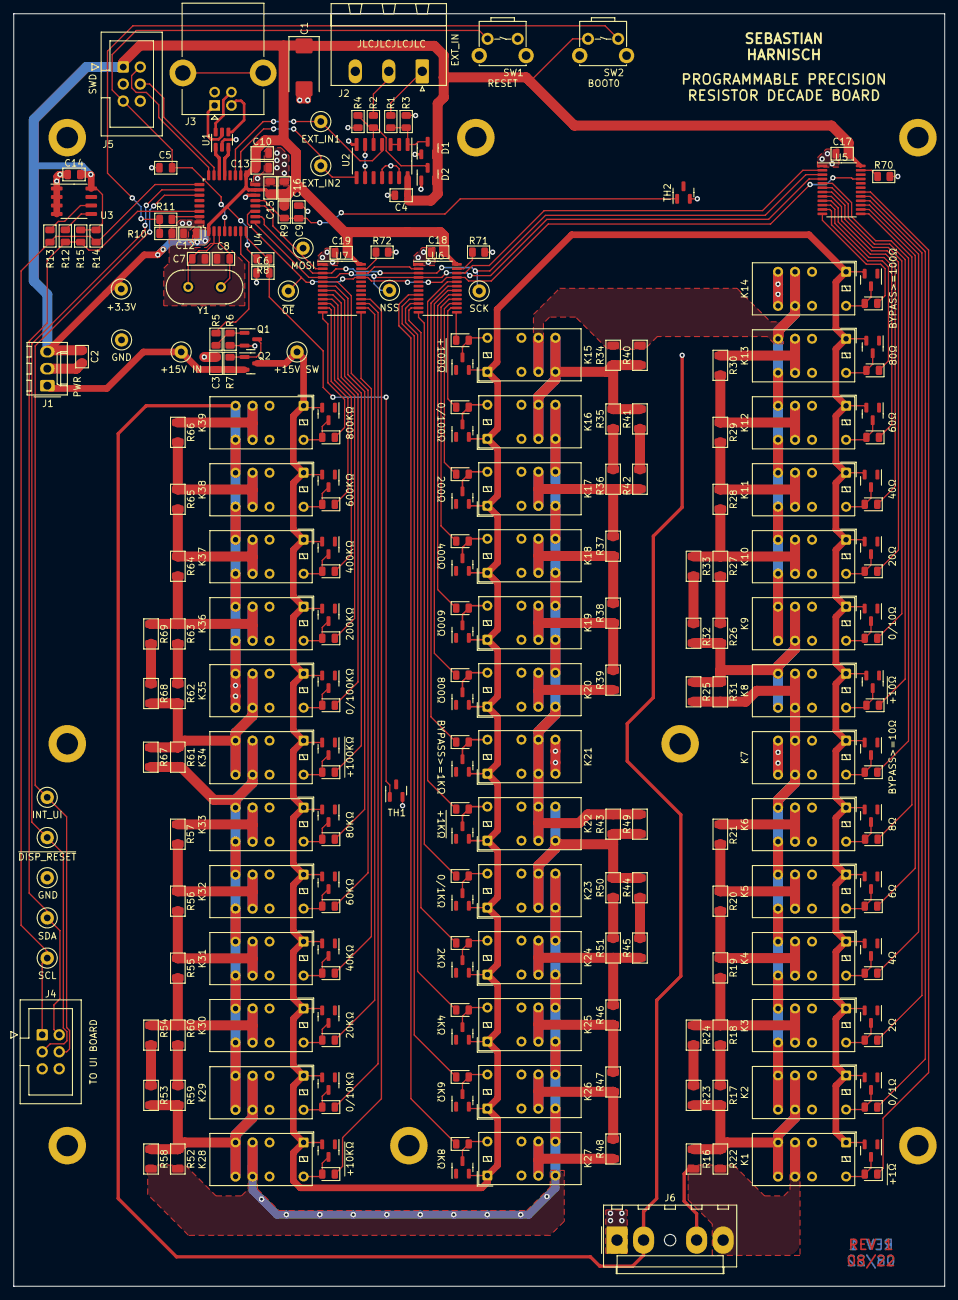
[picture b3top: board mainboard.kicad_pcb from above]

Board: 2 copper layers, 139.0 x 190.0 mm, 253 parts (1 on the bottom side), 171 nets.

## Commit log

2023-08-18 Update readme and media
2023-08-18 Update readme: Change links
2023-08-18 Update name in LICENSE file
2023-08-18 Add mainboard design files
2023-08-18 Solve formating issue in README
2023-08-19 Add UI board design
2023-08-19 Add links to interactive bom
2023-08-19 Update link description
2023-08-19 Add power supply board and minor improvements
2023-08-19 Add front and rear panels
2023-08-19 Move rear panel files
2023-09-19 Remove license file
2023-09-19 Create LICENSE
2023-09-19 Add code for main controller
2024-04-12 Update power supply KiCAD project to v8 and fix incorrect R1 resistor value
2024-05-17 Update README.md
    Add note regarding the necessity of an external EMI filter.
2025-05-05 Update to Kicad v9, new power supply board and other modifications
2025-10-29 Update README with power supply design note
    Added a note about the power supply design changes and documentation discrepancies.
2025-11-02 Fix typos and enhance safety warnings in README
    Updated warnings and notes regarding power supply safety and design changes.
